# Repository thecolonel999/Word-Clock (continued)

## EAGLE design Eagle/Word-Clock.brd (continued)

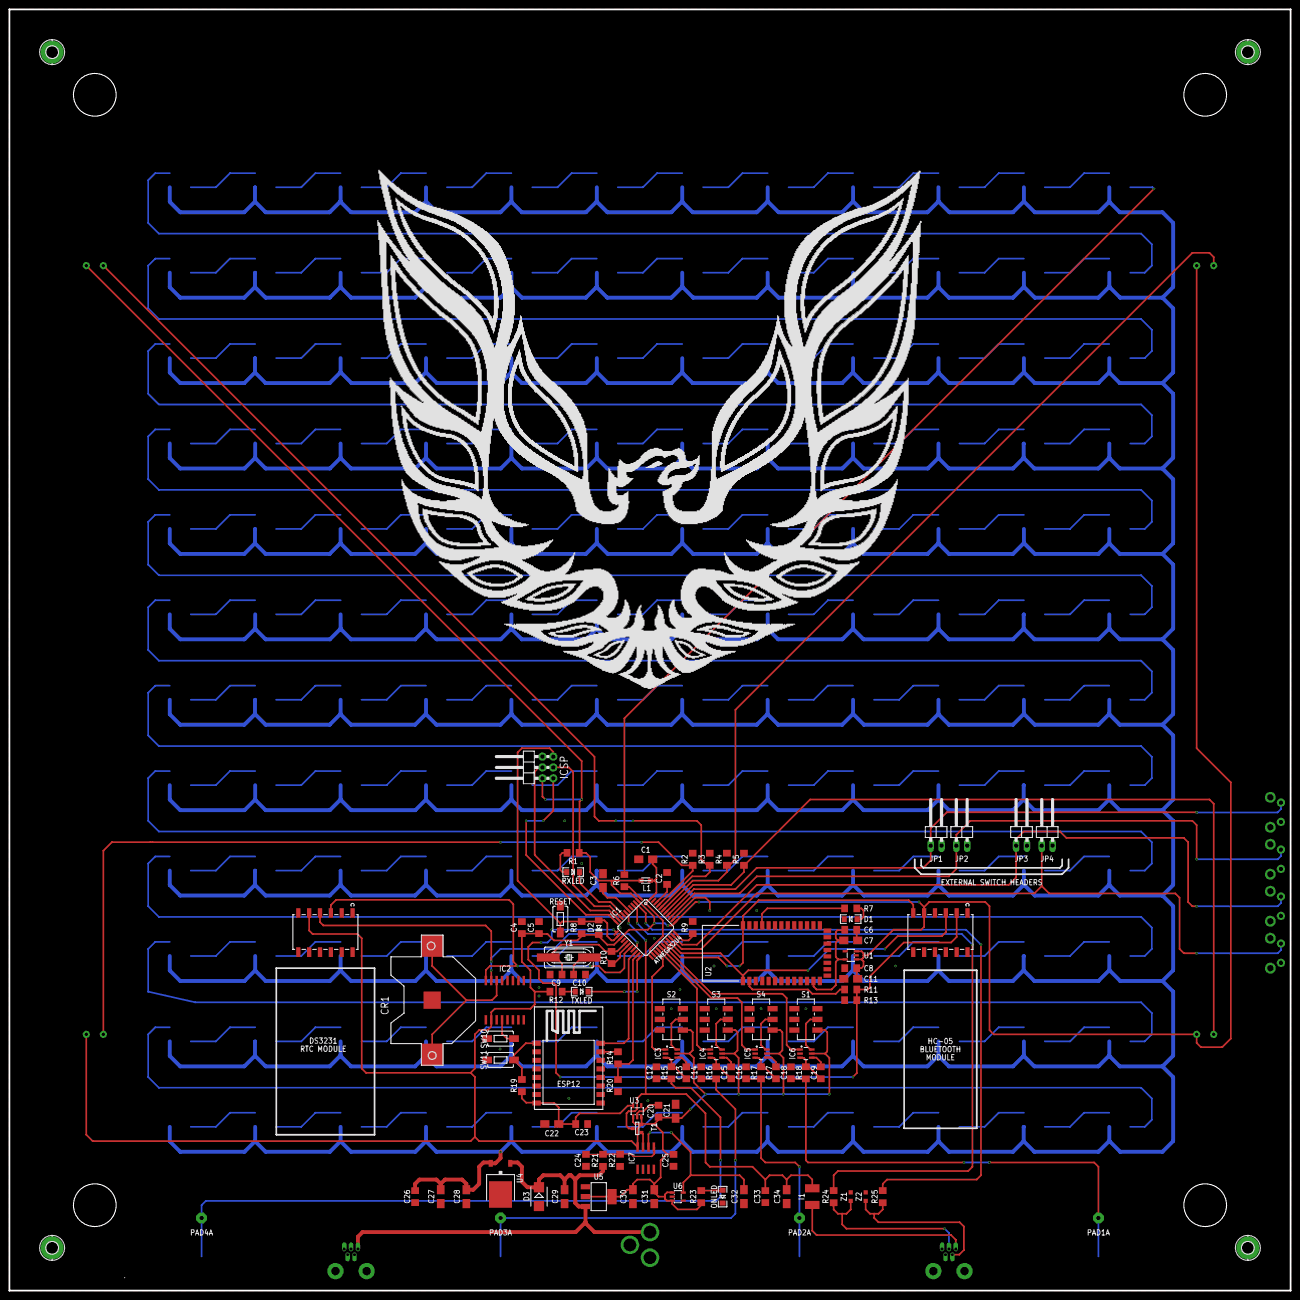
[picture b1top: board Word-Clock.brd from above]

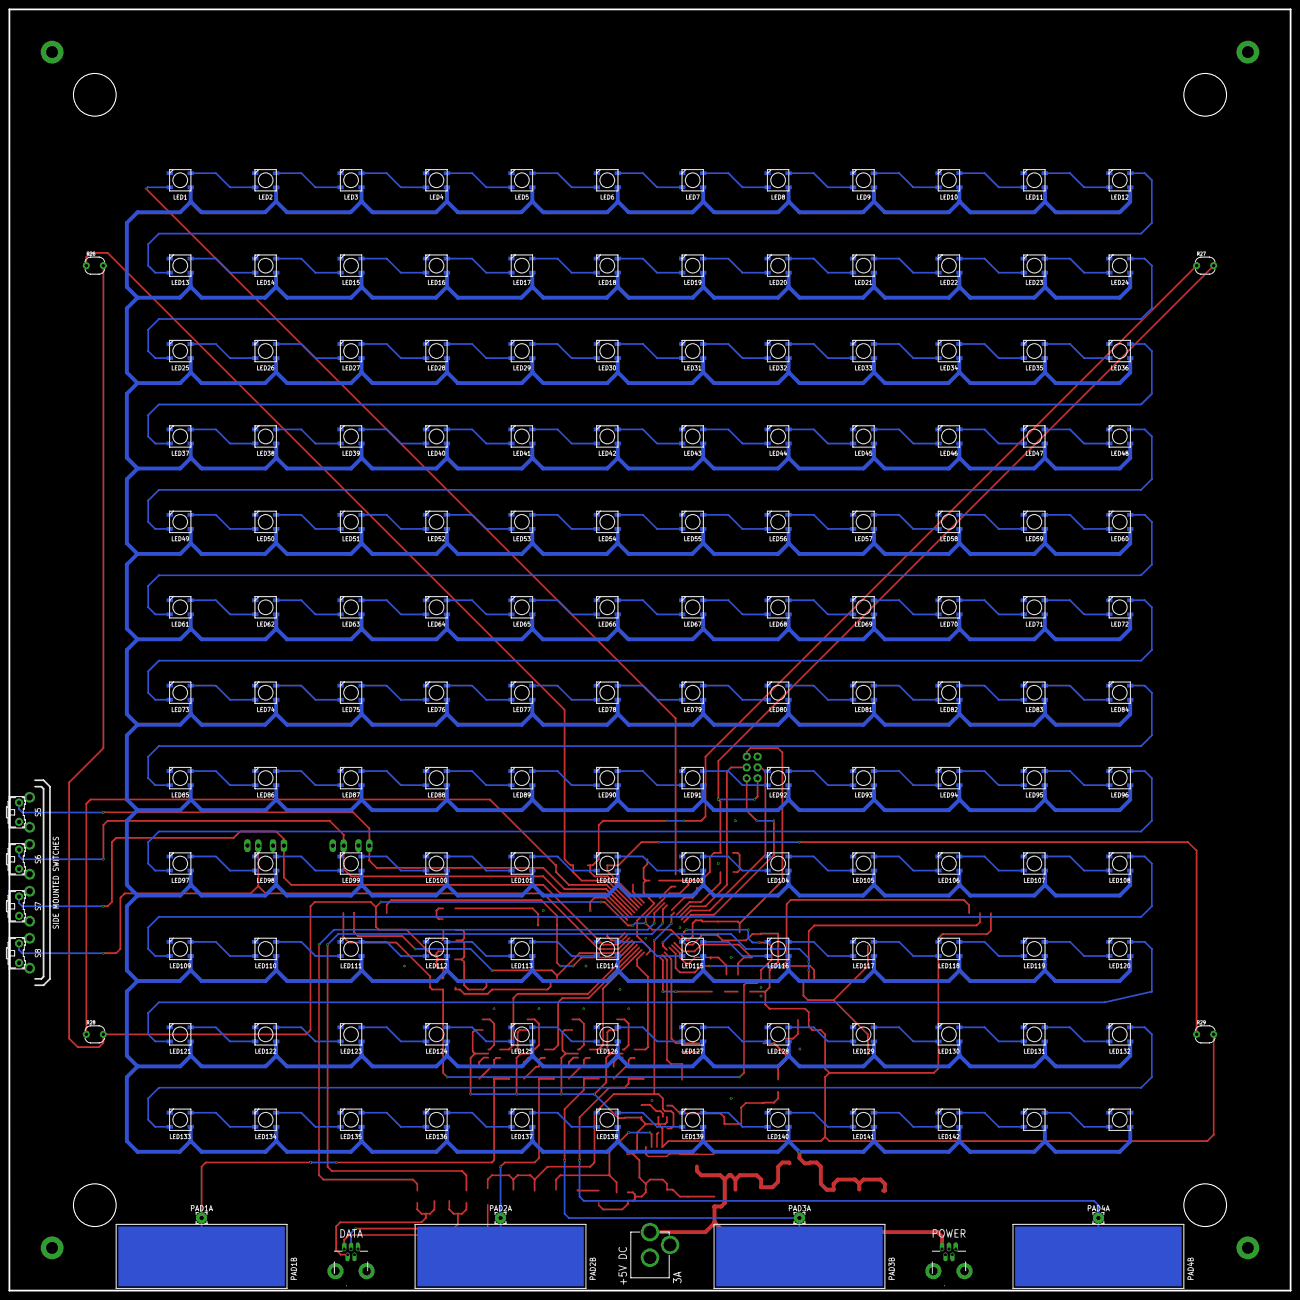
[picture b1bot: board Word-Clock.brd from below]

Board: 2 copper layers, 300.0 x 300.0 mm, 268 parts (163 on the bottom side), 217 nets.

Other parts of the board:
U$1: FIREBIRD2

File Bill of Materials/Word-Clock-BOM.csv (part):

"Part";"Value";"Device";"Package";"Description";"FARNELL";"MF";"MPN";"OC_FARNELL";"OC_NEWARK";"PROD_ID";"VALUE";
"+5VDC";"POWER_JACKPTH";"POWER_JACKPTH";"POWER_JACK_PTH";"Power Jack";"";"";"";"";"";"CONN-08197";"";
"BLUETOOTH";"BLUETOOTH";"M06SMD-FEMALE-V2";"1X06-SMD-FEMALE-V2";"Header 6";"";"";"";"";"";"";"";
"C1";"1uF";"CPOL-EUC/6032-28R";"C/6032-28R";"POLARIZED CAPACITOR, European symbol";"";"";"";"";"";"";"";
"C2";"100n";"C-EUC1206";"C1206";"CAPACITOR, European symbol";"";"";"";"";"";"";"";
"C3";"1uF";"CPOL-EUC/6032-28R";"C/6032-28R";"POLARIZED CAPACITOR, European symbol";"";"";"";"";"";"";"";
"C4";"100n";"C-EUC1206";"C1206";"CAPACITOR, European symbol";"";"";"";"";"";"";"";
"C5";"100n";"C-EUC1206";"C1206";"CAPACITOR, European symbol";"";"";"";"";"";"";"";
"C6";"100n";"C-EUC1206";"C1206";"CAPACITOR, European symbol";"";"";"";"";"";"";"";
"C7";"1u";"CPOL-EUSMCA";"SMC_A";"POLARIZED CAPACITOR, European symbol";"";"";"";"";"";"";"";
"C8";"100n";"C-EUC1206";"C1206";"CAPACITOR, European symbol";"";"";"";"";"";"";"";
"C9";"22p";"C-EUC1206";"C1206";"CAPACITOR, European symbol";"";"";"";"";"";"";"";
"C10";"22p";"C-EUC1206";"C1206";"CAPACITOR, European symbol";"";"";"";"";"";"";"";
"C11";"1u";"CPOL-EUSMCA";"SMC_A";"POLARIZED CAPACITOR, European symbol";"";"";"";"";"";"";"";
"C12";"100n";"C-EUC1206";"C1206";"CAPACITOR, European symbol";"";"";"";"";"";"";"";
"C13";"100n";"C-EUC1206";"C1206";"CAPACITOR, European symbol";"";"";"";"";"";"";"";
"C14";"100n";"C-EUC1206";"C1206";"CAPACITOR, European symbol";"";"";"";"";"";"";"";
"C15";"100n";"C-EUC1206";"C1206";"CAPACITOR, European symbol";"";"";"";"";"";"";"";
"C16";"100n";"C-EUC1206";"C1206";"CAPACITOR, European symbol";"";"";"";"";"";"";"";
"C17";"100n";"C-EUC1206";"C1206";"CAPACITOR, European symbol";"";"";"";"";"";"";"";
"C18";"100n";"C-EUC1206";"C1206";"CAPACITOR, European symbol";"";"";"";"";"";"";"";
"C19";"100n";"C-EUC1206";"C1206";"CAPACITOR, European symbol";"";"";"";"";"";"";"";
"C20";"100n";"C-EUC1206";"C1206";"CAPACITOR, European symbol";"";"";"";"";"";"";"";
"C21";"1u";"CPOL-EUSMCA";"SMC_A";"POLARIZED CAPACITOR, European symbol";"";"";"";"";"";"";"";
"C22";"1u";"CPOL-EUC/6032-28R";"C/6032-28R";"POLARIZED CAPACITOR, European symbol";"";"";"";"";"";"";"";
"C23";"100n";"C-EUC1206";"C1206";"CAPACITOR, European symbol";"";"";"";"";"";"";"";
"C24";"100n";"C-EUC1206";"C1206";"CAPACITOR, European symbol";"";"";"";"";"";"";"";
"C25";"100n";"C-EUC1206";"C1206";"CAPACITOR, European symbol";"";"";"";"";"";"";"";
"C26";"100n";"C-EUC1206";"C1206";"CAPACITOR, European symbol";"";"";"";"";"";"";"";
"C27";"10u";"CPOL-EUC/6032-28R";"C/6032-28R";"POLARIZED CAPACITOR, European symbol";"";"";"";"";"";"";"";
"C28";"10u";"CPOL-EUC/6032-28R";"C/6032-28R";"POLARIZED CAPACITOR, European symbol";"";"";"";"";"";"";"";
"C29";"10u";"CPOL-EUC/6032-28R";"C/6032-28R";"POLARIZED CAPACITOR, European symbol";"";"";"";"";"";"";"";
"C30";"10u";"CPOL-EUC/6032-28R";"C/6032-28R";"POLARIZED CAPACITOR, European symbol";"";"";"";"";"";"";"";
"C31";"1u";"CPOL-EUC/6032-28R";"C/6032-28R";"POLARIZED CAPACITOR, European symbol";"";"";"";"";"";"";"";
"C32";"1u";"CPOL-EUC/6032-28R";"C/6032-28R";"POLARIZED CAPACITOR, European symbol";"";"";"";"";"";"";"";
"C33";"100n";"C-EUC1206";"C1206";"CAPACITOR, European symbol";"";"";"";"";"";"";"";
"C34";"10u";"CPOL-EUC/6032-28R";"C/6032-28R";"POLARIZED CAPACITOR, European symbol";"";"";"";"";"";"";"";
"CR1";"CR2032";"CR2032SMT";"CR2032-SMD";"";"";"";"";"";"";"";"";
"D1";"BLUE";"LED-BLUE1206";"LED-1206";"Blue LEDs for production use";"";"";"";"";"";"DIO-09911";"BLUE";
"D2";"CD1206-S01575";"DIODE-MINIMELF";"MINIMELF";"DIODE";"";"";"";"";"";"";"";
"D3";"M7";"DIODE-SMB";"SMB";"DIODE";"";"";"";"";"";"";"";
"DATA";"USBDATA";"USBMOLEX";"USB-MINIB-THM-MOLEX";"USB Connectors";"";"";"";"";"";"";"";
"DS1";"DS3231";"M06SMD-FEMALE-V2";"1X06-SMD-FEMALE-V2";"Header 6";"";"";"";"";"";"";"";
"ESP1";"ESP12";"ESP-12";"ESP-12";"";"";"";"";"";"";"";"";
"H1";"";"MOUNT-PAD-ROUND2.8";"2,8-PAD";"MOUNTING PAD, round";"";"";"";"";"";"";"";
"H2";"";"MOUNT-PAD-ROUND2.8";"2,8-PAD";"MOUNTING PAD, round";"";"";"";"";"";"";"";
"H3";"";"MOUNT-PAD-ROUND2.8";"2,8-PAD";"MOUNTING PAD, round";"";"";"";"";"";"";"";
"H4";"";"MOUNT-PAD-ROUND2.8";"2,8-PAD";"MOUNTING PAD, round";"";"";"";"";"";"";"";
"I1";"MF-MSMF050-2 500mA";"L-EUL1812";"L1812";"INDUCTOR, European symbol";"";"";"";"";"";"";"";
"IC1";"ATMEGA32U4TQFP-44";"ATMEGA32U4TQFP-44";"TQFP44";"Atmel 44-pin 8-bit Microcontroller with 32KBytes of ISP Flash and USB Controller";"";"";"";"";"";"";"";
"IC2";"DS3231/SO";"DS3231/SO";"SO16W";"";"";"";"";"";"";"";"";
"IC3";"AT42QT1010SOT23";"AT42QT1010SOT23";"SOT23-6";"";"";"";"";"";"";"";"";
"IC4";"AT42QT1010SOT23";"AT42QT1010SOT23";"SOT23-6";"";"";"";"";"";"";"";"";
"IC5";"AT42QT1010SOT23";"AT42QT1010SOT23";"SOT23-6";"";"";"";"";"";"";"";"";
"IC6";"AT42QT1010SOT23";"AT42QT1010SOT23";"SOT23-6";"";"";"";"";"";"";"";"";
"IC7";"LMV358IDGKR";"LMV358MX";"SO08";"Dual General Purpose, Low Voltage, Rail-to-Rail Output Operational Amplifiers";"";"";"";"";"";"";"";
"ICSP";"ICSP";"PINHD-2X3/90";"2X03/90";"PIN HEADER";"";"";"";"";"";"";"";
"JP1";"";"PINHD-1X2/90";"1X02/90";"PIN HEADER";"";"";"";"";"";"";"";
"JP2";"";"PINHD-1X2/90";"1X02/90";"PIN HEADER";"";"";"";"";"";"";"";
"JP3";"";"PINHD-1X2/90";"1X02/90";"PIN HEADER";"";"";"";"";"";"";"";
"JP4";"";"PINHD-1X2/90";"1X02/90";"PIN HEADER";"";"";"";"";"";"";"";
"L1";"MH2029-300Y";"WE-CBF_0805";"0805";"SMD EMI Suppression Ferrite Beads";"";"";"";"";"";"";"";
"LED1";"WS2812B";"WS2812B";"WS2812B";"";"";"";"";"";"";"";"";
"LED2";"WS2812B";"WS2812B";"WS2812B";"";"";"";"";"";"";"";"";
"LED3";"WS2812B";"WS2812B";"WS2812B";"";"";"";"";"";"";"";"";
"LED4";"WS2812B";"WS2812B";"WS2812B";"";"";"";"";"";"";"";"";
"LED5";"WS2812B";"WS2812B";"WS2812B";"";"";"";"";"";"";"";"";
"LED6";"WS2812B";"WS2812B";"WS2812B";"";"";"";"";"";"";"";"";
"LED7";"WS2812B";"WS2812B";"WS2812B";"";"";"";"";"";"";"";"";
"LED8";"WS2812B";"WS2812B";"WS2812B";"";"";"";"";"";"";"";"";
"LED9";"WS2812B";"WS2812B";"WS2812B";"";"";"";"";"";"";"";"";
"LED10";"WS2812B";"WS2812B";"WS2812B";"";"";"";"";"";"";"";"";
"LED11";"WS2812B";"WS2812B";"WS2812B";"";"";"";"";"";"";"";"";
"LED12";"WS2812B";"WS2812B";"WS2812B";"";"";"";"";"";"";"";"";
"LED13";"WS2812B";"WS2812B";"WS2812B";"";"";"";"";"";"";"";"";
"LED14";"WS2812B";"WS2812B";"WS2812B";"";"";"";"";"";"";"";"";
"LED15";"WS2812B";"WS2812B";"WS2812B";"";"";"";"";"";"";"";"";
"LED16";"WS2812B";"WS2812B";"WS2812B";"";"";"";"";"";"";"";"";
"LED17";"WS2812B";"WS2812B";"WS2812B";"";"";"";"";"";"";"";"";
"LED18";"WS2812B";"WS2812B";"WS2812B";"";"";"";"";"";"";"";"";
"LED19";"WS2812B";"WS2812B";"WS2812B";"";"";"";"";"";"";"";"";
"LED20";"WS2812B";"WS2812B";"WS2812B";"";"";"";"";"";"";"";"";
"LED21";"WS2812B";"WS2812B";"WS2812B";"";"";"";"";"";"";"";"";
"LED22";"WS2812B";"WS2812B";"WS2812B";"";"";"";"";"";"";"";"";
"LED23";"WS2812B";"WS2812B";"WS2812B";"";"";"";"";"";"";"";"";
"LED24";"WS2812B";"WS2812B";"WS2812B";"";"";"";"";"";"";"";"";
"LED25";"WS2812B";"WS2812B";"WS2812B";"";"";"";"";"";"";"";"";
"LED26";"WS2812B";"WS2812B";"WS2812B";"";"";"";"";"";"";"";"";
"LED27";"WS2812B";"WS2812B";"WS2812B";"";"";"";"";"";"";"";"";
"LED28";"WS2812B";"WS2812B";"WS2812B";"";"";"";"";"";"";"";"";
"LED29";"WS2812B";"WS2812B";"WS2812B";"";"";"";"";"";"";"";"";
"LED30";"WS2812B";"WS2812B";"WS2812B";"";"";"";"";"";"";"";"";
"LED31";"WS2812B";"WS2812B";"WS2812B";"";"";"";"";"";"";"";"";
"LED32";"WS2812B";"WS2812B";"WS2812B";"";"";"";"";"";"";"";"";
"LED33";"WS2812B";"WS2812B";"WS2812B";"";"";"";"";"";"";"";"";
"LED34";"WS2812B";"WS2812B";"WS2812B";"";"";"";"";"";"";"";"";
"LED35";"WS2812B";"WS2812B";"WS2812B";"";"";"";"";"";"";"";"";
"LED36";"WS2812B";"WS2812B";"WS2812B";"";"";"";"";"";"";"";"";
"LED37";"WS2812B";"WS2812B";"WS2812B";"";"";"";"";"";"";"";"";
"LED38";"WS2812B";"WS2812B";"WS2812B";"";"";"";"";"";"";"";"";
"LED39";"WS2812B";"WS2812B";"WS2812B";"";"";"";"";"";"";"";"";
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
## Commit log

2015-10-07 First Iteration of Arduino Code
2015-10-07 Schematic V1.0
2015-10-07 Schematic & PCB V1.1
2015-10-07 Schematic & PCB V1.2
2015-10-08 New Code
2015-10-09 Updated BOM
2015-10-14 Power Consumption Calculations
2015-10-21 V1.2 PCB
2015-10-30 V1.3 PCB
